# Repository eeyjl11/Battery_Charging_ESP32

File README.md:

# Battery_Charging_ESP32
 ESP32 S3 with integrated li-ion battery charging.
 
 ## MCP73831T-5ACI_OT
 For charging battery.
 
 ## DW01A and FS8205
 Handles battery protection.
 
 ## AMS1117-3.3
 3.3V Voltage regulator for ESP32.
 
 ## TO DO:
 - Bill of materials
 - Position file for JLCPCB pick and place
 - Generate gerber and drill files

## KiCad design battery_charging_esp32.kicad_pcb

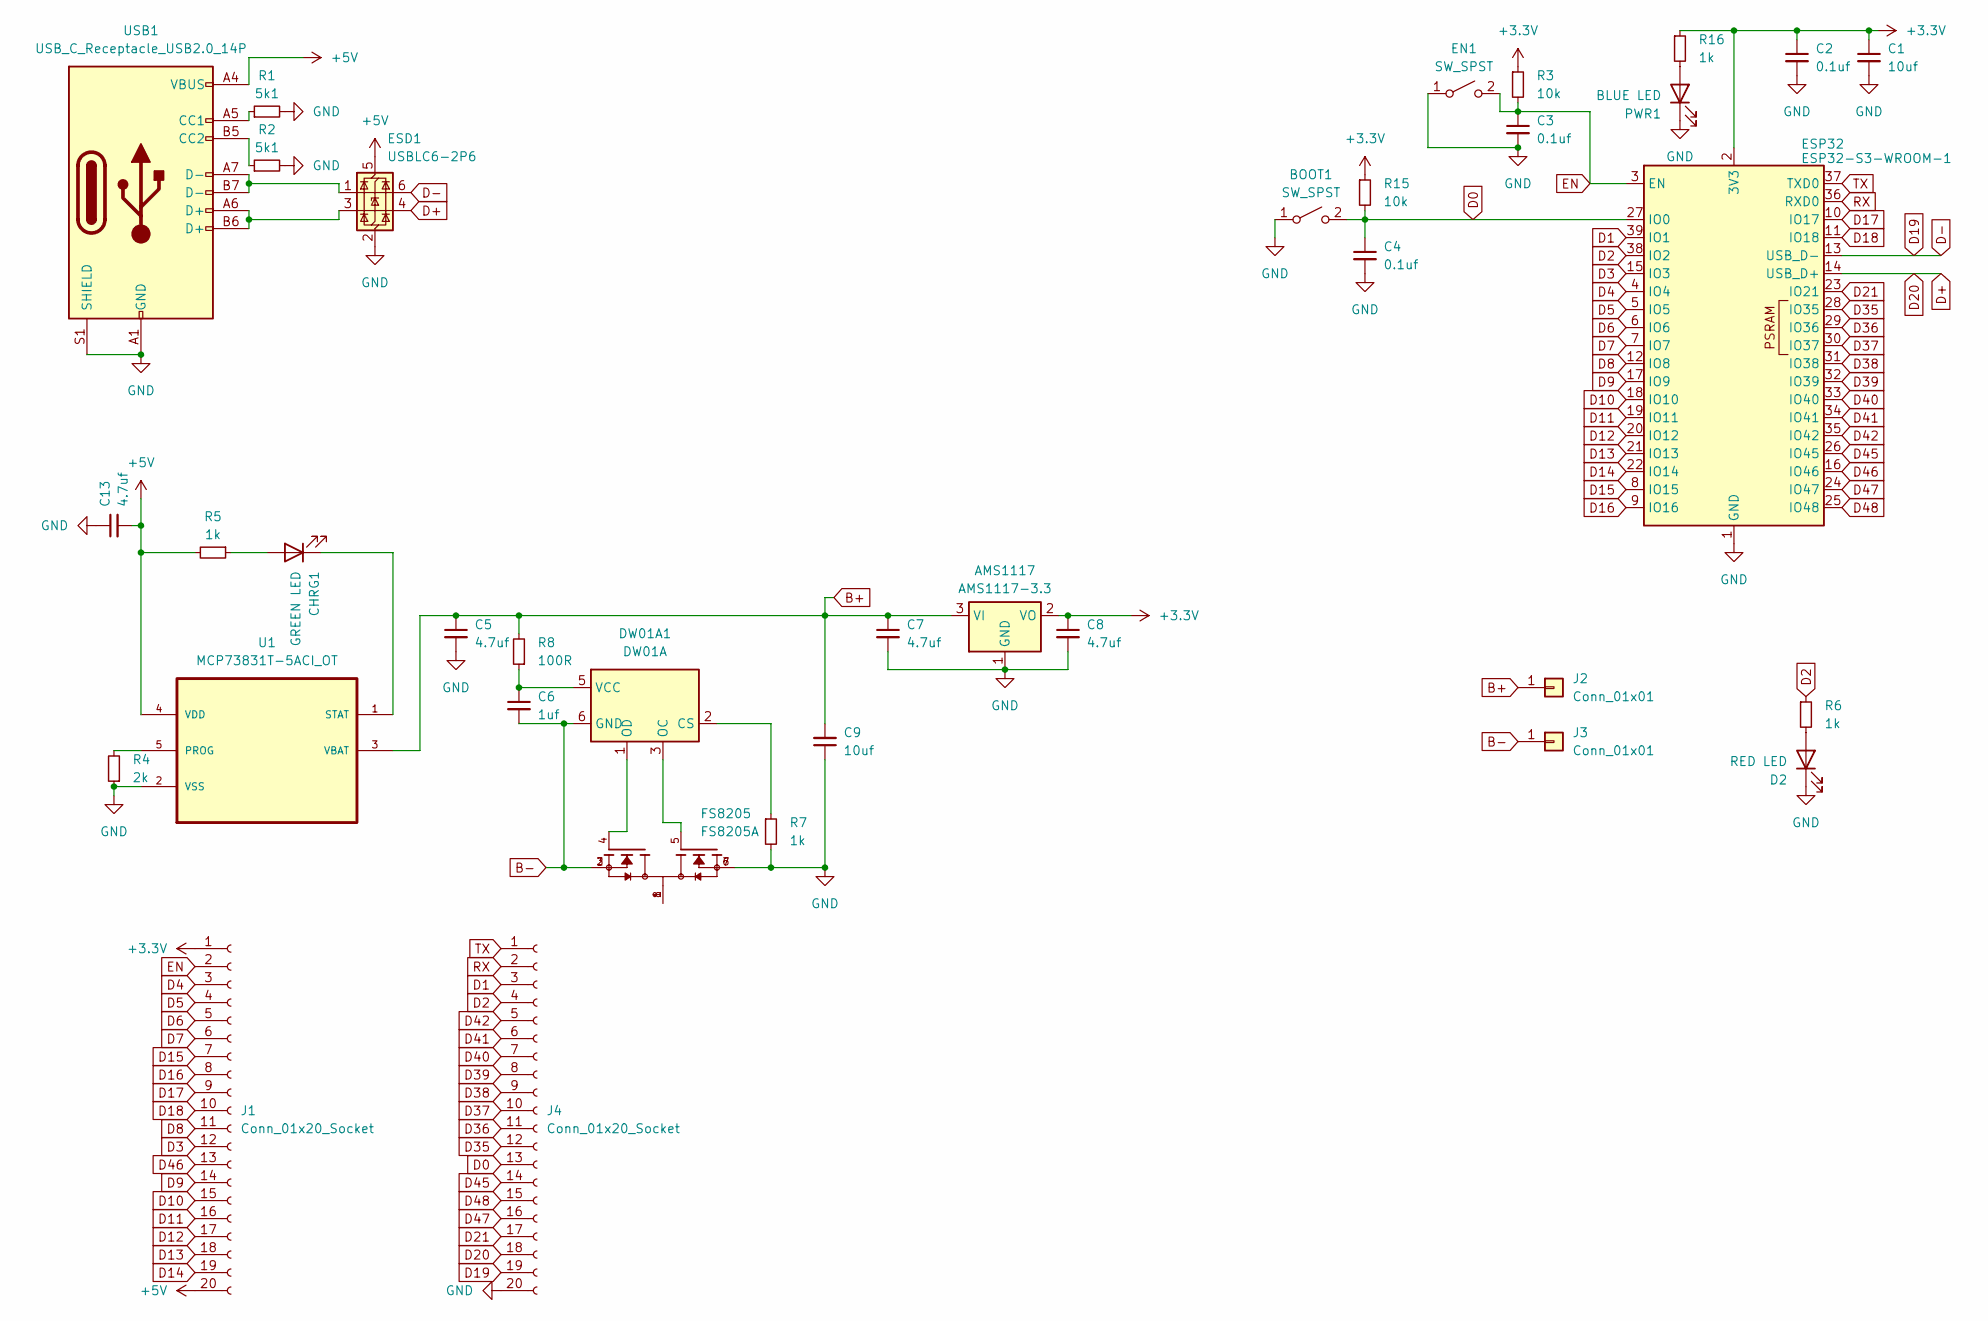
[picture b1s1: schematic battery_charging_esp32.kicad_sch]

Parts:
AMS1117: AMS1117-3.3; SOT-223-3_TabPin2
BOOT1: SW_SPST; SW_Push_SPST_NO_Alps_SKRK
C1, C9: 10uf; C_0603_1608Metric
C2, C3, C4: 0.1uf; C_0402_1005Metric
C5, C7, C8, C13: 4.7uf; C_0603_1608Metric
C6: 1uf; C_0402_1005Metric
CHRG1: GREEN LED; LED_0603_1608Metric
D2: RED LED; LED_0603_1608Metric
DW01A1: DW01A; SOT-23-6
EN1: SW_SPST; SW_Push_SPST_NO_Alps_SKRK
ESD1: USBLC6-2P6; SOT-666
ESP32: ESP32-S3-WROOM-1
FS8205: FS8205A; SOP65P640X120-8N; PARTREV 1.7
J1, J4: Conn_01x20_Socket; PinSocket_1x20_P2.54mm_Vertical
J2, J3: Conn_01x01; SolderWire-0.1sqmm_1x01_D0.4mm_OD1mm
PWR1: BLUE LED; LED_0603_1608Metric
R1, R2: 5k1; R_0402_1005Metric
R3, R15: 10k; R_0805_2012Metric
R4: 2k; R_0402_1005Metric
R5, R6, R7, R16: 1k; R_0402_1005Metric
R8: 100R; R_0402_1005Metric
U1: MCP73831T-5ACI_OT; SOT95P280X145-5N; MPN MCP73831T-5ACI/OT
USB1: USB_C_Receptacle_USB2.0_14P; USB_C_Receptacle_GCT_USB4105-xx-A_16P_TopMnt_Horizontal

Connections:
+3.3V: AMS1117.2 (VO), C1.1, C2.1, C8.1, ESP32.2 (3V3), J1.1, R3.1, R15.1, R16.1
+5V: C13.2, ESD1.5 (VBUS), J1.20, R5.2, U1.4 (VDD), USB1.A4 (VBUS), USB1.A9 (VBUS), USB1.B4 (VBUS), USB1.B9 (VBUS)
B+: AMS1117.3 (VI), C5.1, C7.1, C9.2, J2.1, R8.2, U1.3 (VBAT)
B-: C6.2, DW01A1.6 (GND), FS8205.2, FS8205.3, J3.1
D0: BOOT1.2 (B), C4.1, ESP32.27 (IO0), J4.13, R15.2
D1: ESP32.39 (IO1), J4.3
D2: ESP32.38 (IO2), J4.4, R6.1
D3: ESP32.15 (IO3), J1.12
D4: ESP32.4 (IO4), J1.3
D5: ESP32.5 (IO5), J1.4
D6: ESP32.6 (IO6), J1.5
D7: ESP32.7 (IO7), J1.6
D8: ESP32.12 (IO8), J1.11
D9: ESP32.17 (IO9), J1.14
D10: ESP32.18 (IO10), J1.15
D11: ESP32.19 (IO11), J1.16
D12: ESP32.20 (IO12), J1.17
D13: ESP32.21 (IO13), J1.18
D14: ESP32.22 (IO14), J1.19
D15: ESP32.8 (IO15), J1.7
D16: ESP32.9 (IO16), J1.8
D17: ESP32.10 (IO17), J1.9
D18: ESP32.11 (IO18), J1.10
D21: ESP32.23 (IO21), J4.17
D35: ESP32.28 (IO35), J4.12
D36: ESP32.29 (IO36), J4.11
D37: ESP32.30 (IO37), J4.10
D38: ESP32.31 (IO38), J4.9
D39: ESP32.32 (IO39), J4.8
D40: ESP32.33 (IO40), J4.7
D41: ESP32.34 (IO41), J4.6
D42: ESP32.35 (IO42), J4.5
D45: ESP32.26 (IO45), J4.14
D46: ESP32.16 (IO46), J1.13
D47: ESP32.24 (IO47), J4.16
D48: ESP32.25 (IO48), J4.15
D+: ESD1.4 (I/O2), ESP32.14 (USB_D+), J4.18
D-: ESD1.6 (I/O1), ESP32.13 (USB_D-), J4.19
EN: C3.1, EN1.2 (B), ESP32.3 (EN), J1.2, R3.2
GND: AMS1117.1 (GND), BOOT1.1 (A), C1.2, C2.2, C3.2, C4.2, C5.2, C7.2, C8.2, C9.1, C13.1, D2.1 (K), EN1.1 (A), ESD1.2 (GND), ESP32.1 (GND), ESP32.40 (GND), ESP32.41 (GND), FS8205.6, FS8205.7, J4.20, PWR1.1 (K), R1.2, R2.2, R4.1, R7.2, U1.2 (VSS), USB1.A1 (GND), USB1.A12 (GND), USB1.B1 (GND), USB1.B12 (GND), USB1.S1 (SHIELD)
unnamed: CHRG1.2 (A), R5.1
unnamed: CHRG1.1 (K), U1.1 (STAT)
unnamed: D2.2 (A), R6.2
unnamed: DW01A1.2 (CS), R7.1
unnamed: DW01A1.3 (OC), FS8205.5
unnamed: DW01A1.1 (OD), FS8205.4
unnamed: C6.1, DW01A1.5 (VCC), R8.1
unnamed: ESD1.1 (I/O1), USB1.A7 (D-), USB1.B7 (D-)
unnamed: ESD1.3 (I/O2), USB1.A6 (D+), USB1.B6 (D+)
unnamed: FS8205.1, FS8205.8
unnamed: PWR1.2 (A), R16.2
unnamed: R4.2, U1.5 (PROG)
unnamed: R1.1, USB1.A5 (CC1)
unnamed: R2.1, USB1.B5 (CC2)
RX: ESP32.36 (RXD0), J4.2
TX: ESP32.37 (TXD0), J4.1

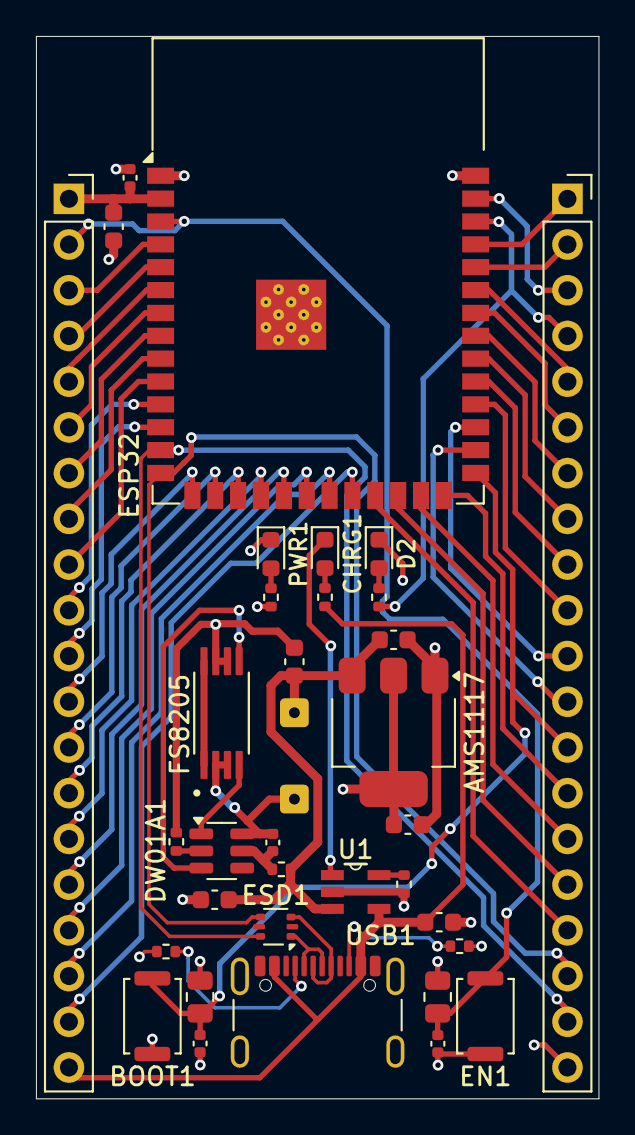
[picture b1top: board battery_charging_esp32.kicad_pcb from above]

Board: 4 copper layers, 31.2 x 59.0 mm, 36 parts (0 on the bottom side), 56 nets.

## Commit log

2025-03-21 Todo list
